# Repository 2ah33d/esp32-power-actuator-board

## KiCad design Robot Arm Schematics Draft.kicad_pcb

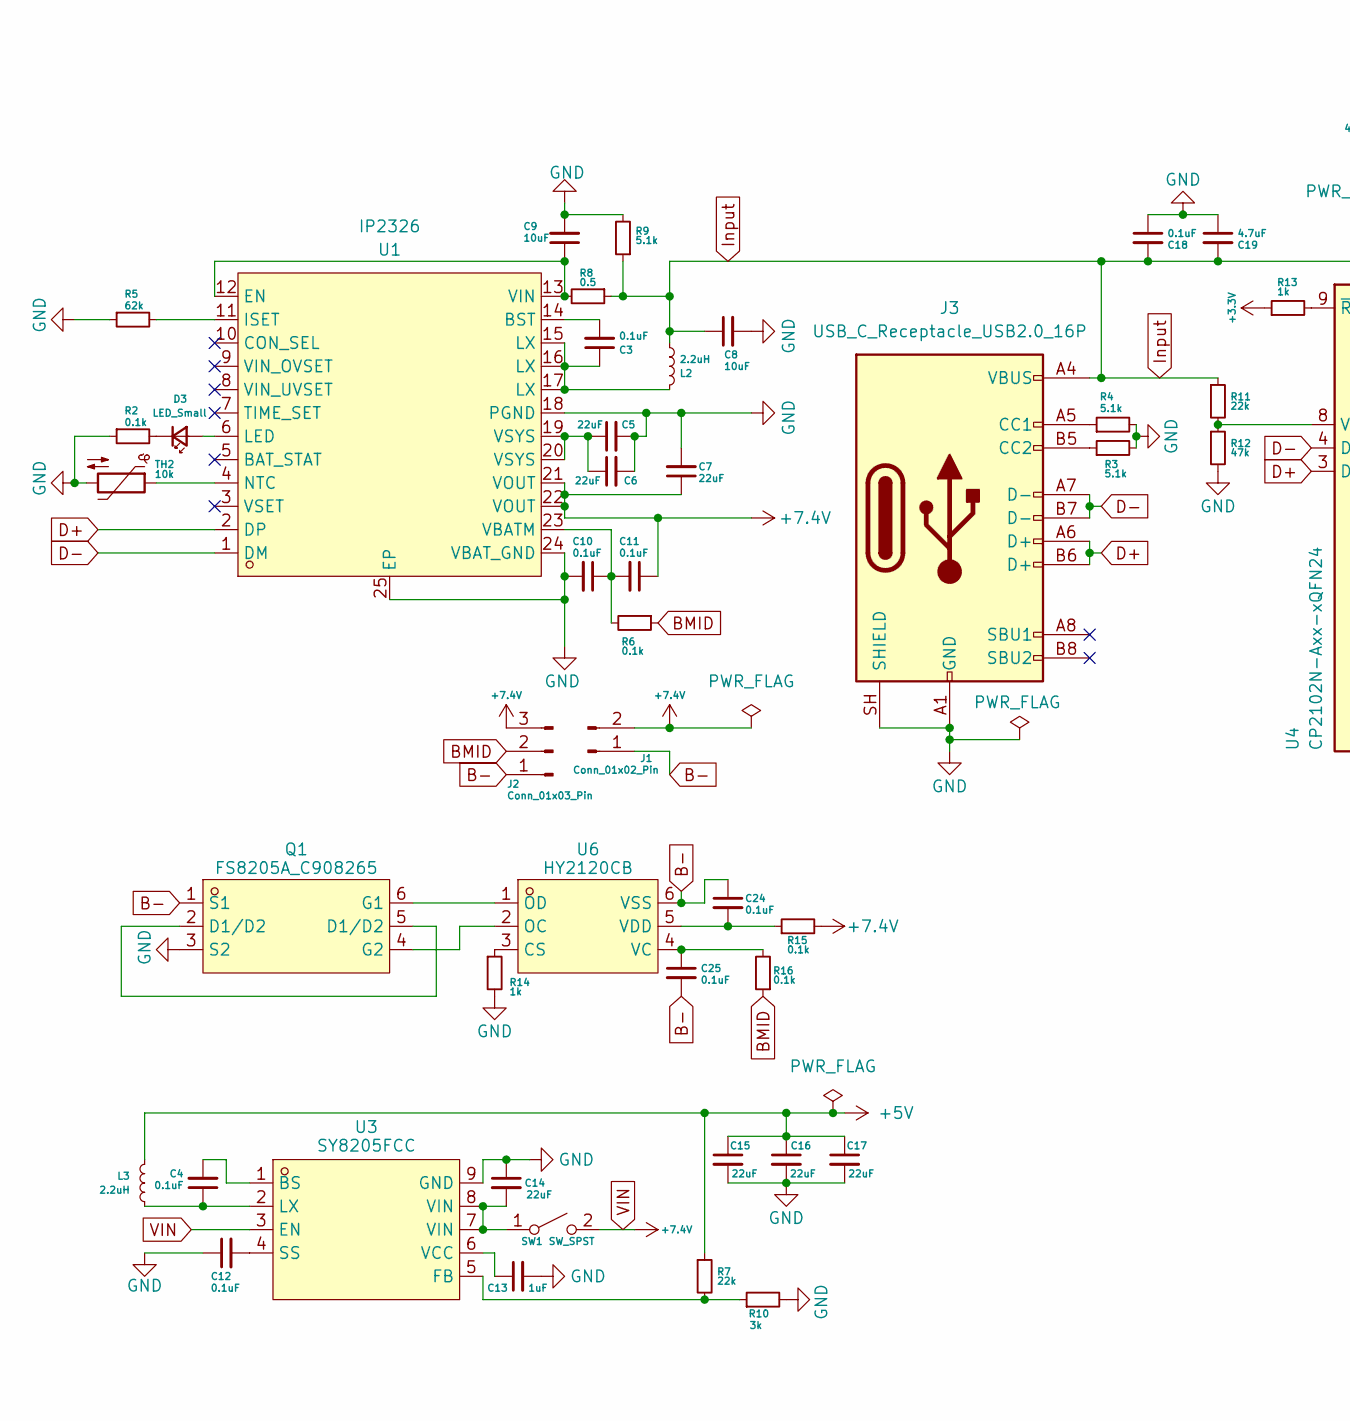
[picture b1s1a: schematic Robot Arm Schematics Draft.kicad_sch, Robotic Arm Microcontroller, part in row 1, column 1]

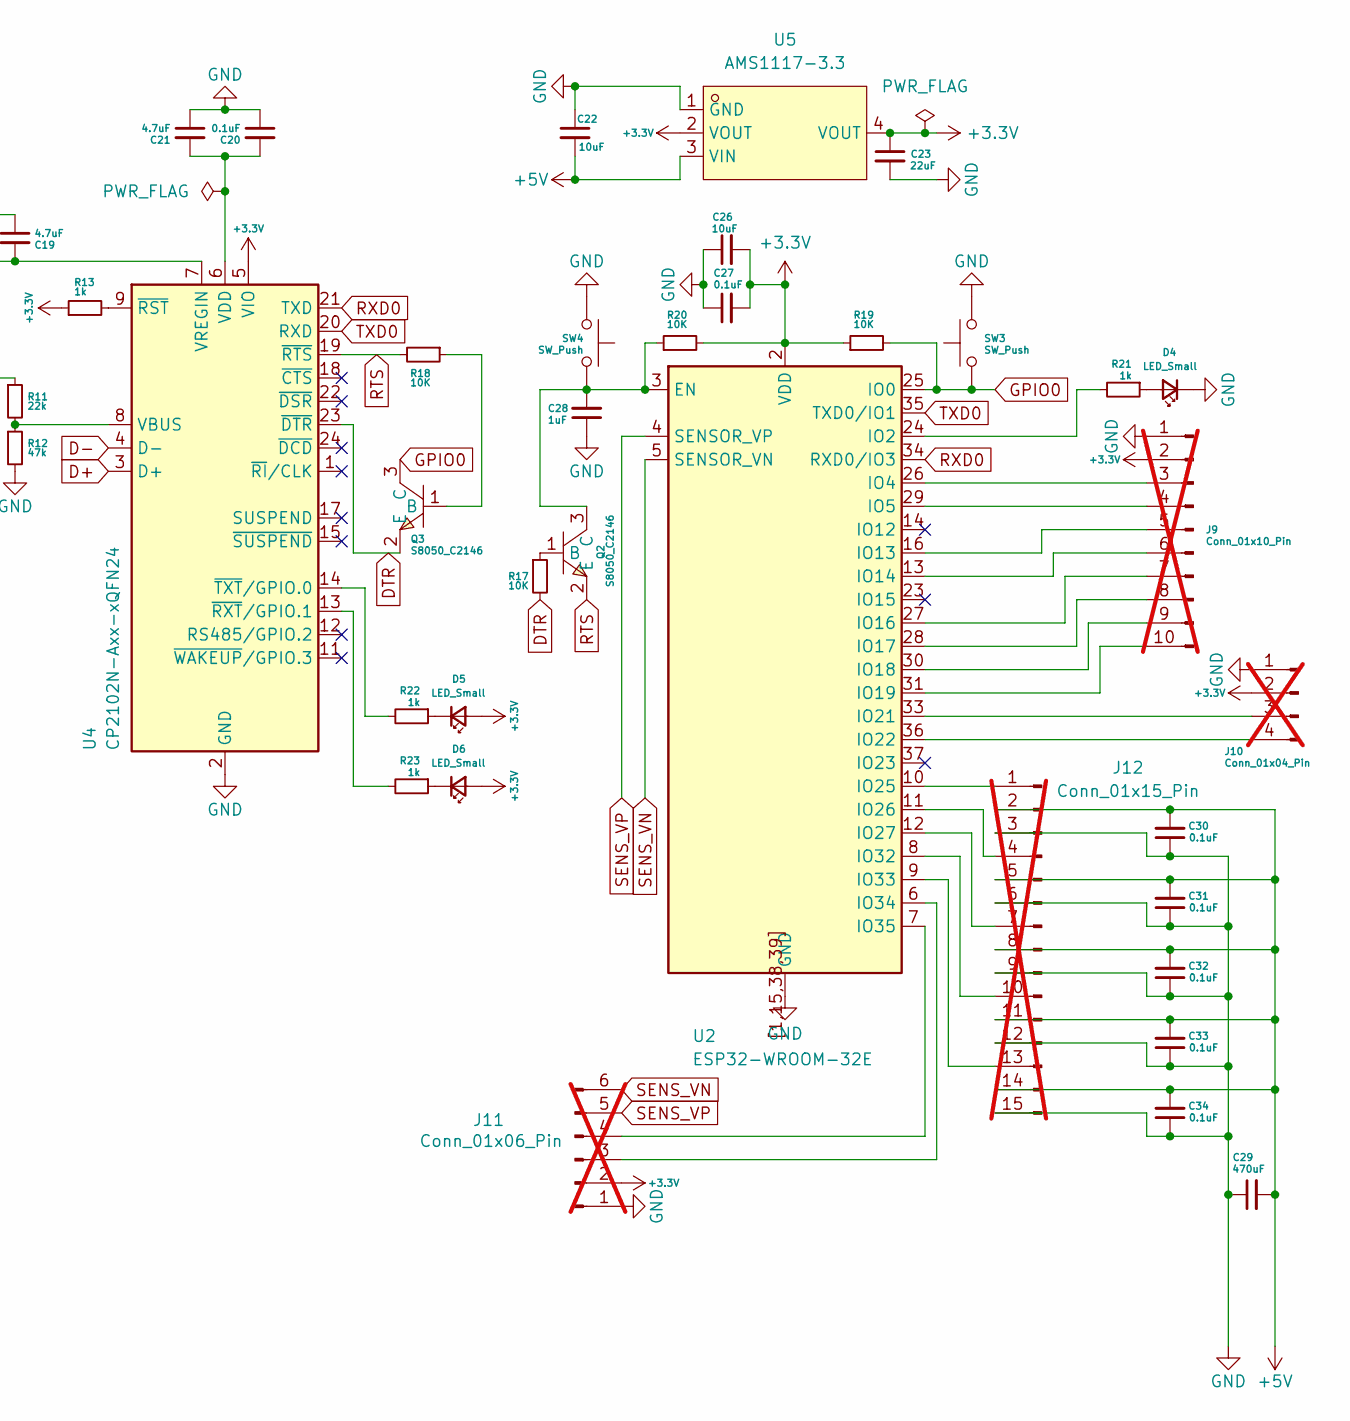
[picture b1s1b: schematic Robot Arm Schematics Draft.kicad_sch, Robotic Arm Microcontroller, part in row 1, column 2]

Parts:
C3, C4, C10, C11, C12, C18, C20, C24, C25, C27, C30, C31, C32, C33, C34: 0.1uF; C_0603_1608Metric; LCSC C14663
C5, C6, C7, C14, C15, C16, C17, C23: 22uF; C_0603_1608Metric; LCSC C2762594
C8, C9, C22, C26: 10uF; C_0603_1608Metric; LCSC C70225
C13, C28: 1uF; C_0603_1608Metric; LCSC C15849
C19, C21: 4.7uF; C_0603_1608Metric; LCSC C19666
C29: 470uF; CP_Elec_8x10; LCSC C165531
D3, D4, D5, D6: LED_Small; LED_0603_1608Metric; LCSC C2286
J1: Conn_01x02_Pin; AMASS_XT60PW-M_1x02_P7.20mm_Horizontal; LCSC C98732
J2: Conn_01x03_Pin; JST_XH_S3B-XH-A_1x03_P2.50mm_Horizontal; LCSC C157928
J3: USB_C_Receptacle_USB2.0_16P; USB_C_Receptacle_HRO_TYPE-C-31-M-12; LCSC C165948
J9: Conn_01x10_Pin; PinHeader_1x10_P2.54mm_Vertical; not fitted
J10: Conn_01x04_Pin; FanPinHeader_1x04_P2.54mm_Vertical; not fitted
J11: Conn_01x06_Pin; PinHeader_1x06_P2.54mm_Vertical; not fitted
J12: Conn_01x15_Pin; PinHeader_1x15_P2.54mm_Vertical; not fitted
L2, L3: 2.2uH; L_Taiyo-Yuden_NR-40xx; LCSC C28642347
Q1: FS8205A_C908265; SOT-23-6_L2.9-W1.6-P0.95-LS2.8-BR; MPN FS8205A; LCSC Part C908265
Q2, Q3: S8050_C2146; SOT-23-3_L3.0-W1.7-P0.95-LS2.9-BR; MPN S8050 J3Y(RANGE:200-350); LCSC Part C2146
R2, R6, R15, R16: 0.1k; R_0603_1608Metric; LCSC C22775
R3, R4, R9: 5.1k; R_0603_1608Metric; LCSC C23186
R5: 62k; R_0603_1608Metric; LCSC C23221
R7, R11: 22k; R_0603_1608Metric; LCSC C31850
R8: 0.5; R_0603_1608Metric; LCSC C45312
R10: 3k; R_0603_1608Metric; LCSC C4211
R12: 47k; R_0603_1608Metric; LCSC C25819
R13, R14, R21, R22, R23: 1k; R_0603_1608Metric; LCSC C21190
R17, R18, R19, R20: 10K; R_0603_1608Metric; LCSC C25804
SW1: SW_SPST; SW_SPDT_PCM12; LCSC C221841
SW3, SW4: SW_Push; SW_SPST_PTS645Sx43SMTR92; LCSC C2837531
TH2: 10k; R_0603_1608Metric; LCSC C51597
U1: IP2326; VQFN-24_L4.0-W4.0-P0.50-BL-EP2.5; MPN IP2326; LCSC Part C2832094
U2: ESP32-WROOM-32E; LCSC C701343
U3: SY8205FCC; SOIC-8_L5.0-W4.0-P1.27-LS6.0-BL-EP2.0; MPN SY8205FCC; LCSC Part C111875
U4: CP2102N-Axx-xQFN24; QFN-24-1EP_4x4mm_P0.5mm_EP2.6x2.6mm; LCSC C969151
U5: AMS1117-3.3; SOT-223-3_L6.5-W3.4-P2.30-LS7.0-BR; MPN AMS1117-3.3; LCSC Part C6186
U6: HY2120CB; SOT-23-6_L2.9-W1.6-P0.95-LS2.8-BR; MPN HY2120-CB; LCSC Part C116509

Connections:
+3.3V: C23.1, C26.2, C27.2, D5.2 (A), D6.2 (A), J9.2, J10.2, J11.2, R13.1, R19.1, R20.2, U2.2 (VDD), U4.5 (VIO), U5.2 (VOUT), U5.4 (VOUT)
+5V: C15.1, C16.1, C17.1, C22.2, C29.2, C30.2, C31.2, C32.2, C33.2, C34.2, J12.2, J12.5, J12.8, J12.11, J12.14, L3.1, R7.1, U5.3 (VIN)
B-: C24.1, C25.2, J1.1, J2.1, Q1.1 (S1), U6.6 (VSS)
BMID: J2.2, R6.1, R16.1
D+: J3.A6 (D+), J3.B6 (D+), U1.2 (DP), U4.3 (D+)
D-: J3.A7 (D-), J3.B7 (D-), U1.1 (DM), U4.4 (D-)
DTR: Q3.2 (E), R17.2, U4.23 (~DTR)
GND: C5.2, C6.2, C7.2, C8.2, C9.2, C10.2, C12.1, C13.2, C14.1, C15.2, C16.2, C17.2, C18.1, C19.1, C20.1, C21.1, C22.1, C23.2, C26.1, C27.1, C28.1, C29.1, C30.1, C31.1, C32.1, C33.1, C34.1, D4.1 (K), J3.A1 (GND), J3.A12 (GND), J3.B1 (GND), J3.B12 (GND), J3.SH (SHIELD), J9.1, J10.1, J11.1, J12.3, J12.6, J12.9, J12.12, J12.15, Q1.3 (S2), R2.1, R3.2, R4.2, R5.1, R9.2, R10.2, R12.2, R14.2, SW3.2, SW4.2, TH2.2, U1.18 (PGND), U1.24 (VBAT_GND), U1.25 (EP), U2.1 (GND), U2.15 (GND), U2.38 (GND), U2.39 (GND), U2.[1,15,38,39] (GND), U3.9 (GND), U4.2 (GND), U4.25 (GND), U5.1 (GND)
GPIO0: Q3.3 (C), R19.2, SW3.1, U2.25 (IO0)
Input: C8.1, C18.2, C19.2, J3.A4 (VBUS), J3.A9 (VBUS), J3.B4 (VBUS), J3.B9 (VBUS), L2.2, R8.1, R9.1, R11.1, U4.7 (VREGIN)
unnamed: C3.1, L2.1, U1.15 (LX), U1.16 (LX), U1.17 (LX)
unnamed: C5.1, C6.1, U1.19 (VSYS), U1.20 (VSYS)
unnamed: D3.2 (A), U1.6 (LED)
unnamed: D3.1 (K), R2.2
unnamed: D4.2 (A), R21.1
unnamed: D5.1 (K), R22.1
unnamed: D6.1 (K), R23.1
unnamed: J3.A5 (CC1), R4.1
unnamed: J3.B5 (CC2), R3.1
unnamed: J9.3, U2.26 (IO4)
unnamed: J9.4, U2.29 (IO5)
unnamed: J9.5, U2.16 (IO13)
unnamed: J9.6, U2.13 (IO14)
unnamed: J9.7, U2.27 (IO16)
unnamed: J9.8, U2.28 (IO17)
unnamed: J9.9, U2.30 (IO18)
unnamed: J9.10, U2.31 (IO19)
unnamed: J10.3, U2.33 (IO21)
unnamed: J10.4, U2.36 (IO22)
unnamed: J11.3, U2.6 (IO34)
unnamed: J11.4, U2.7 (IO35)
unnamed: J12.1, U2.10 (IO25)
unnamed: J12.4, U2.11 (IO26)
unnamed: J12.7, U2.12 (IO27)
unnamed: J12.10, U2.8 (IO32)
unnamed: J12.13, U2.9 (IO33)
unnamed: Q1.2 (D1/D2), Q1.5 (D1/D2)
unnamed: Q1.6 (G1), U6.1 (OD)
unnamed: Q1.4 (G2), U6.2 (OC)
unnamed: Q2.1 (B), R17.1
unnamed: C28.2, Q2.3 (C), R20.1, SW4.1, U2.3 (EN)
unnamed: Q3.1 (B), R18.1
unnamed: C14.2, SW1.1 (A), U3.7 (VIN), U3.8 (VIN)
unnamed: C3.2, U1.14 (BST)
unnamed: C9.1, R8.2, U1.12 (EN), U1.13 (VIN)
unnamed: R5.2, U1.11 (ISET)
unnamed: TH2.1, U1.4 (NTC)
unnamed: C10.1, C11.2, R6.2, U1.23 (VBATM)
unnamed: R21.2, U2.24 (IO2)
unnamed: C4.2, U3.1 (BS)
unnamed: R7.2, R10.1, U3.5 (FB)
unnamed: C4.1, L3.2, U3.2 (LX)
unnamed: C12.2, U3.4 (SS)
unnamed: C13.1, U3.6 (VCC)
unnamed: R11.2, R12.1, U4.8 (VBUS)
unnamed: C20.2, C21.2, U4.6 (VDD)
unnamed: R13.2, U4.9 (~RST)
unnamed: R23.2, U4.13 (~RXT/GPIO.1)
unnamed: R22.2, U4.14 (~TXT/GPIO.0)
unnamed: R14.1, U6.3 (CS)
unnamed: C25.1, R16.2, U6.4 (VC)
unnamed: C24.2, R15.1, U6.5 (VDD)
RTS: Q2.2 (E), R18.2, U4.19 (~RTS)
RXD0: U2.34 (RXD0/IO3), U4.21 (TXD)
SENS_VN: J11.6, U2.5 (SENSOR_VN)
SENS_VP: J11.5, U2.4 (SENSOR_VP)
TXD0: U2.35 (TXD0/IO1), U4.20 (RXD)
VIN: C7.1, C11.1, J1.2, J2.3, R15.2, SW1.2 (B), U1.21 (VOUT), U1.22 (VOUT), U3.3 (EN)

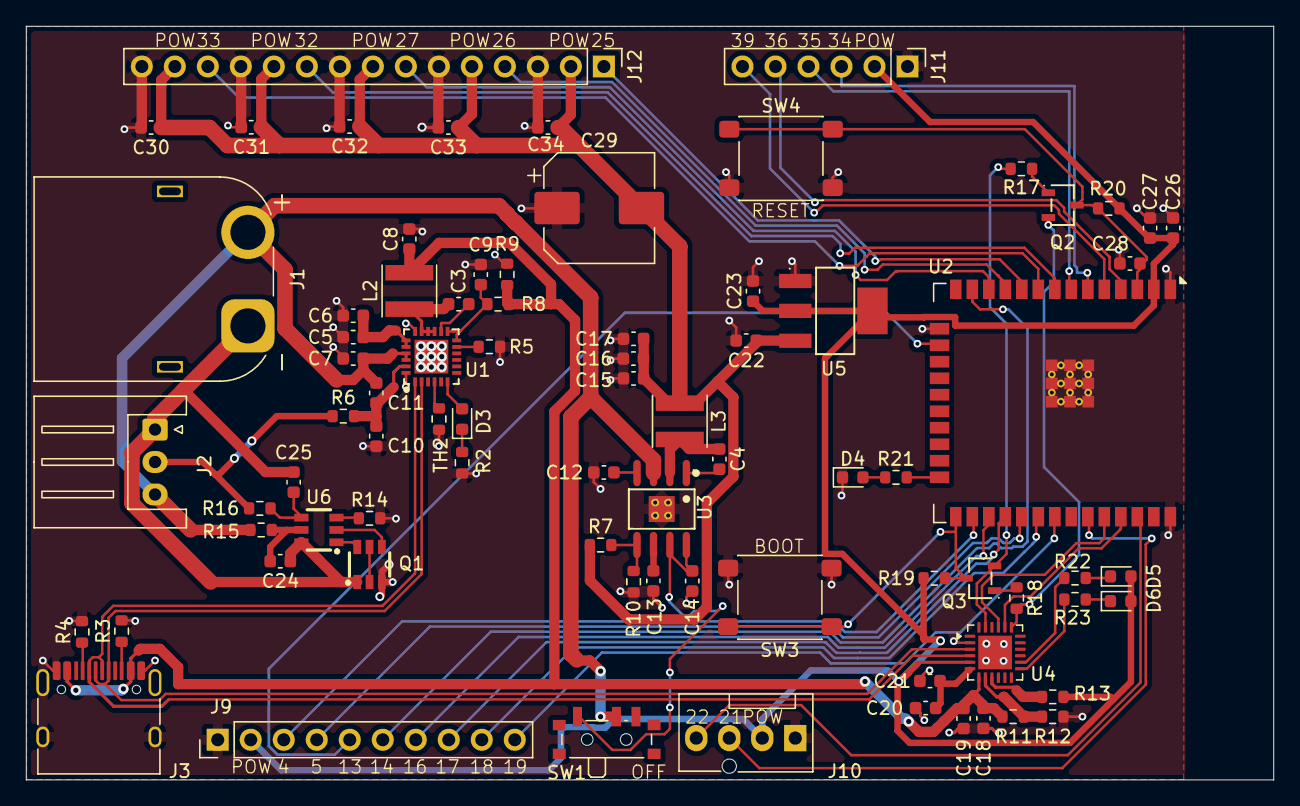
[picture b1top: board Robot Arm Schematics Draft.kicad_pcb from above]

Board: 2 copper layers, 96.0 x 58.0 mm, 80 parts (0 on the bottom side), 68 nets.

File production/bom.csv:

Designator,Footprint,Quantity,Value,LCSC Part #
"C10, C11, C12, C18, C20, C24, C25, C27, C3, C30, C31, C32, C33, C34, C4",0603,15,0.1uF,C14663
"C13, C28",0603,2,1uF,C15849
"C14, C15, C16, C17, C23, C5, C6, C7",0603,8,22uF,C2762594
"C19, C21",0603,2,4.7uF,C19666
"C22, C26, C8, C9",0603,4,10uF,C70225
C29,CP_Elec_8x10,1,470uF,C165531
"D3, D4, D5, D6",0603,4,LED_Small,C2286
J1,AMASS_XT60PW-M_1x02_P7.20mm_Horizontal,1,Conn_01x02_Pin,C98732
J2,JST_XH_S3B-XH-A_1x03_P2.50mm_Horizontal,1,Conn_01x03_Pin,C157928
J3,USB_C_Receptacle_HRO_TYPE-C-31-M-12,1,USB_C_Receptacle_USB2.0_16P,C165948
"L2, L3",L_Taiyo-Yuden_NR-40xx,2,2.2uH,C28642347
Q1,SOT-23-6_L2.9-W1.6-P0.95-LS2.8-BR,1,FS8205A_C908265,C908265
"Q2, Q3",SOT-23-3_L3.0-W1.7-P0.95-LS2.9-BR,2,S8050_C2146,C2146
R10,0603,1,3k,C4211
"R11, R7",0603,2,22k,C31850
R12,0603,1,47k,C25819
"R13, R14, R21, R22, R23",0603,5,1k,C21190
"R15, R16, R2, R6",0603,4,0.1k,C22775
"R17, R18, R19, R20",0603,4,10K,C25804
"R3, R4, R9",0603,3,5.1k,C23186
R5,0603,1,62k,C23221
R8,0603,1,0.5,C45312
SW1,SW_SPDT_PCM12,1,SW_SPST,C221841
"SW3, SW4",SW_SPST_PTS645Sx43SMTR92,2,SW_Push,C2837531
TH2,0603,1,10k,C51597
U1,VQFN-24_L4.0-W4.0-P0.50-BL-EP2.5,1,IP2326,C2832094
U2,ESP32-WROOM-32E,1,ESP32-WROOM-32E,C701343
U3,SOIC-8_L5.0-W4.0-P1.27-LS6.0-BL-EP2.0,1,SY8205FCC,C111875
U4,QFN-24-1EP_4x4mm_P0.5mm_EP2.6x2.6mm,1,CP2102N-Axx-xQFN24,C969151
U5,SOT-223-3_L6.5-W3.4-P2.30-LS7.0-BR,1,AMS1117-3.3,C6186
U6,SOT-23-6_L2.9-W1.6-P0.95-LS2.8-BR,1,HY2120CB,C116509
